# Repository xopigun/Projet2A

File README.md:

# Banc de test CAN — G69-BANC-001

Outil interne du **groupe 69** (ENSEA 2A, projet « Conception d'une Électronique Modulaire
(Bus CAN) ») servant à valider le standard CAN commun et les ICD produits avec les groupes
partenaires.

Le banc est **générique** : aucun code n'est spécifique à un groupe partenaire, les besoins
particuliers passent par de la configuration. Les quatre projets partenaires (Cobot RMD-X,
Ecomarathon, Formula Student, MIR1000) sont traités au même niveau.

Auteurs (ordre alphabétique) : Samuel GOMRI, Dylan KIATI, Hugo MATHOUX.

---

## ⚠ À faire avant la première mise sous tension

Ces deux points sont des **modifications matérielles** sur chaque Nucleo-G431KB. Les ignorer
donne des symptômes qui ressemblent à une panne et non à une erreur de montage.

1. **Retirer le cavalier HW1**, livré fermé entre `CN4` broche 5 (`D2` = PA12) et `CN4`
   broche 4 (`GND`) — UM2397 §5.1 et §6.1. PA12 est `FDCAN1_TX` : laissé à la masse, il
   place le bus en **état dominant permanent** et bloque toute communication.

2. **Souder les ponts SB9 et SB10** pour connecter le quartz 24 MHz. En sortie d'usine la
   carte démarre sur le **HSI** (UM2397 §6.5, Table 9), dont la précision de ±1 % dépasse
   plus du double la tolérance admissible de 0,485 % à 500 kbit/s. Tant que ce n'est pas
   fait, compiler avec `-DBENCH_CLOCK_SOURCE=HSI` : le firmware émet un avertissement à la
   compilation, affiche `HSI - NON VALIDE` sur l'écran et signale le défaut dans son
   heartbeat, et `canbench` refuse alors de prononcer un verdict de réussite.

**Procédure de mise en route pas à pas : [docs/bringup.md](docs/bringup.md).** Elle amène
trois cartes neuves à un bus qui communique, en validant l'horloge, le temps de bit et
l'encodage **avant** tout câblage grâce au bouclage interne du FDCAN.

Brochage, terminaisons et injection de fautes : [docs/pinout.md](docs/pinout.md).

---

## Démarrage rapide

### Prérequis

| Outil | Version | Rôle |
|---|---|---|
| git | ≥ 2.30 | sous-modules |
| CMake | ≥ 3.24 | presets version 6 |
| Ninja | ≥ 1.10 | générateur |
| `arm-none-eabi-gcc` | ≥ 12 | firmwares |
| `gcc` ou `clang` | — | tests unitaires natifs |
| Python | ≥ 3.10 | outils PC et génération depuis l'ICD |
| STM32CubeProgrammer **ou** OpenOCD | — | programmation (facultatif) |

### Cloner

```bash
git clone --recursive <url> banc-can
cd banc-can
```

Si le dépôt a été cloné sans `--recursive` :

```bash
git submodule update --init --recursive
```

### Compiler et exécuter les tests unitaires (aucun matériel)

```bash
cmake --preset host
cmake --build --preset host
ctest --preset host
```

### Compiler un firmware

Un preset par nœud : `n1`, `n2`, `n3` (Nucleo-G431KB) et `n4` (Blue Pill STM32F103).

```bash
cmake --preset n1
cmake --build --preset n1
```

### Programmer un nœud

```bash
cmake --build --preset n1 --target flash_n1
```

`STM32_Programmer_CLI` et `openocd` sont cherchés dans le `PATH` puis dans les emplacements
d'installation usuels ; le premier trouvé est utilisé. Pour forcer :
`cmake --preset n1 -DBENCH_FLASH_TOOL=openocd`.

### Installer les outils PC

```bash
python -m pip install -e "pc[dev]"
```

### Premier test, sans matériel

Toutes les sous-commandes fonctionnent sur le bus `virtual` de python-can, avec un
simulateur qui reproduit N1 à N4 (ARM/GO et heartbeat compris) :

```bash
canbench --interface virtual --simulate arbitration --cycles 100
canbench --interface virtual --simulate encoding
canbench --interface virtual --simulate faults
canbench --interface virtual --simulate busload --measure 2
```

`--simulate` démarre un simulateur reproduisant N1 à N4. **Aucun verdict de réussite n'est
prononcé sur le bus virtuel** : le simulateur reproduit le comportement attendu, il ne le
démontre pas. Les rapports produits portent la mention correspondante.

### Interface graphique

Pour une démonstration, ou simplement pour piloter le banc sans ligne de commande, il
existe un **logiciel Windows**, `BancCAN.exe`. Il s'ouvre dans sa propre fenêtre, se
connecte depuis le bouton « Connexion » (simulation ou CANable), et s'arrête quand on
ferme la fenêtre. Le bouton « Aide » explique chaque indicateur, chaque test et chaque
faute. L'exécutable n'est pas versionné ; il se reconstruit en une minute :

```bash
python -m pip install pyinstaller
```

```bash
python pc/build_exe.py
```

Le fichier produit est `dist/BancCAN.exe`. Pour que le logiciel pilote un CANable réel,
installer le pilote python-can correspondant **avant** de le construire
(`python -m pip install -e "pc[slcan]"` ou `"pc[gs-usb]"`) : il est alors embarqué.
Le firmware candleLight (`gs_usb`) demande en outre la bibliothèque système **libusb**,
absente par défaut sous Windows : installer `libusb-package` avant la construction, qui
embarque alors `libusb-1.0.dll`. Tant qu'elle manque, la fenêtre « Connexion »
l'indique au lieu de proposer une connexion vouée à l'échec. Le firmware `slcan` n'en a
pas besoin.

Sans construire l'exécutable, **double-cliquer sur `lancer_banc.bat`** donne la même
interface dans le navigateur. Le navigateur s'ouvre sur
<http://127.0.0.1:8765> et affiche le bus en direct, l'état des nœuds tiré de leurs
heartbeats, les trames décodées par l'ICD, les tests T3, T4 et T6 avec leur rapport
téléchargeable, et l'injection de fautes par `BENCH_CFG`.

Sans argument, l'interface tourne en **simulation** : un bandeau le rappelle en permanence
et aucun verdict n'y vaut preuve. Sur le banc réel :

```bash
lancer_banc.bat gs_usb
```

L'équivalent en ligne de commande est `canbench --interface virtual gui`. L'interface
n'ajoute aucune dépendance et n'a aucune logique de test propre : elle appelle les mêmes
fonctions que `canbench`.

### Premier test sur le banc réel

Le CANable 2.0 est supporté en firmware candleLight (`gs_usb`) et en `slcan` :

```bash
canbench --interface gs_usb  monitor
canbench --interface slcan --channel COM7 arbitration --cycles 1000
```

---

## Organisation du dépôt

| Répertoire | Contenu |
|---|---|
| `icd/` | `bench_icd.yaml` — **source unique** des identifiants, signaux et encodages |
| `tools/codegen/` | génération depuis l'ICD : C, Python, DBC, LaTeX |
| `firmware/common/` | code indépendant du microcontrôleur — aucun en-tête HAL |
| `firmware/ports/` | couches matérielles : `g431_fdcan`, `f103_bxcan` |
| `firmware/boards/` | `board.h` — **tout** le brochage, et nulle part ailleurs |
| `firmware/vendor/` | sous-modules ST épinglés (HAL, CMSIS) |
| `firmware/tests_host/` | tests unitaires natifs du code commun |
| `pc/canbench/` | outil en ligne de commande `canbench` |
| `scripts/` | `bit_timing.py`, `bus_load.py` |
| `docs/` | plan, architecture, brochage, bit timing, protocole de validation, extraits LaTeX |

Le code généré depuis l'ICD (`firmware/common/icd_gen/`, `pc/canbench/icd_gen.py`) **ne
doit pas être édité à la main** : un test de CI vérifie qu'il est à jour.

## Sous-modules

Versions épinglées ; licences relevées dans les dépôts aux versions indiquées.

| Sous-module | Tag | Licence |
|---|---|---|
| `cmsis_core` | `v5.9.0_20250520` | Apache-2.0 |
| `cmsis_device_g4` | `v1.2.6` | Apache-2.0 |
| `cmsis_device_f1` | `v4.3.5` | Apache-2.0 |
| `stm32g4xx_hal_driver` | `v1.2.7` | BSD-3-Clause |
| `stm32f1xx_hal_driver` | `v1.1.10` | BSD-3-Clause |

Le projet lui-même est sous licence MIT — voir [LICENSE](LICENSE).

## Paramètres retenus

| Paramètre | Valeur |
|---|---|
| Débit | 500 kbit/s, CAN 2.0A *classic* (identifiants 11 bits) |
| Point d'échantillonnage | 87,50 % exactement, identique sur G431 et F103 |
| Tolérance d'oscillateur | 0,485 % — voir [docs/bit_timing.md](docs/bit_timing.md) |
| G431 | horloge FDCAN 80 MHz, BRP 10, 16 tq (1+13+2), SJW 2 |
| F103 | APB1 36 MHz, BRP 9, 8 tq (1+6+1), SJW 1 |

## Documentation

- [docs/PLAN.md](docs/PLAN.md) — plan de travail, écarts relevés, points à vérifier
- [docs/architecture.md](docs/architecture.md) — couches, flux ISR, machine d'états ARM/GO
- [docs/pinout.md](docs/pinout.md) — brochage, vérifié depuis les `board.h`
- [docs/bit_timing.md](docs/bit_timing.md) — calcul et justification du bit timing
- [docs/config_logicielle.md](docs/config_logicielle.md) — paramètres FDCAN/bxCAN
- [docs/protocole_validation.md](docs/protocole_validation.md) — les sept tests T1 à T7
- [docs/bringup.md](docs/bringup.md) — procédure de mise en route pas à pas
- [docs/references/README.md](docs/references/README.md) — où trouver les documents de référence

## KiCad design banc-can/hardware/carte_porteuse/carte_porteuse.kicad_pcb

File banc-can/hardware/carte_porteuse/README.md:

# Carte porteuse d'un nœud du banc CAN (v0.2)

Une Nucleo-G431KB s'enfiche dessus. La carte porte le transceiver TJA1051T/3 et ses
découplages, deux borniers pour chaîner le bus (entrée à gauche, sortie à droite), la
terminaison 120 Ω sur cavalier, l'écran OLED, le MPU-6050 (N2) et deux LED d'état.
Plus aucun fil Dupont. À fabriquer en 4 exemplaires.

## Disposition (vue de dessus, arrière en haut)

| Zone | Contenu |
|---|---|
| Bande arrière | bornier d'entrée (fils à gauche), bornier de sortie (fils à droite), fixation M3 H1 |
| Colonne centrale | barrettes de la Nucleo, posée dans la profondeur, **USB vers l'arrière** (câble vers le hub) ; sous elle, le TJA1051, ses 100 nF, les résistances et la fixation H2 ; barrette coudée de l'OLED au bord avant |
| Gauche | barrette coudée du MPU-6050 : le module tient debout au-delà du bord |
| Droite | cavalier TERM, barrette capteurs (non montée), LED **B** (bus-off, jaune) et **E** (erreur, rouge) |

Contour en escalier : 2 050 mm² au lieu de 3 250 mm² pour la v0.1 rectangulaire (−37 %).

## Montage

1. Souder les CMS (U1, C1, C2, R1, R2, R3, R7, R9, R10, D1, D2), puis les barrettes et les borniers.
2. **Avant R9 et R10 : vérifier l'ordre des broches de l'OLED reçu.** GND puis VCC : R9 et R10.
   VCC puis GND : R11 et R12 à la place. Jamais les quatre.
3. Visser la carte sur la plaque du banc (H1, H2, vis M3), **puis** enficher la Nucleo :
   broche 1 de CN3 et CN4 côté USB, flèche « ^ USB ».
4. L'OLED s'enfiche à l'horizontale dans sa barrette coudée et tient debout, à l'envers :
   le firmware retourne l'affichage. Le MPU-6050 de même, sur N2.
5. Cavalier TERM sur le nœud en bout de bus seulement (N4 : câble vers l'interrupteur SW1).

Non montés : R8 (S sur PB6), R11/R12 (OLED en VCC/GND), R4/R5 (tirages I2C, les modules ont
les leurs), J8 (capteurs Hall et 1-Wire, reportés ; tirage 1-Wire sur le module DS18B20).

## Vérifications

**Électrique** : ERC 0 ; DRC 0 erreur, 0 liaison manquante, 0 erreur d'empreinte ; restent
79 avertissements de sérigraphie (contours des barrettes coudées et des borniers qui touchent
volontairement le bord, repères qui se touchent).

**Encombrements** (`verification/encombrement.py`, sur l'export 3D KiCad) : aucun conflit entre
les modules enfichés (Nucleo et sa fiche USB, OLED debout, MPU-6050 debout, fils des borniers,
cavalier, câble capteurs, têtes de vis M3) et les composants. Sous la Nucleo (fond à 10,5 mm),
le plus haut est le corps de la barrette OLED (4,1 mm). Le MPU-6050 commence 2,7 mm sous les
fils du bornier d'entrée. Vue : `openscad verification/assemblage.scad` après
`kicad-cli pcb export stl --subst-models --user-origin 100x100mm -o verification/carte.stl carte_porteuse.kicad_pcb`.

**Solidité** : largeur minimale 19,6 mm ; les parties latérales sont rattachées au corps sur
toute leur longueur (22 et 45 mm) ; deux angles rentrants seulement, loin des borniers ; les
deux vis M3 sont entre les barrettes de la Nucleo, là où s'exerce l'effort d'enfichage. La
plaque du banc devra soutenir les deux coins arrière, sous les borniers, où l'on serre les vis.

**Cours PCB (option Maker)** :

| Règle du cours | Sur la carte |
|---|---|
| Contraintes mécaniques et fixations d'abord | 2 trous M3 de 3,2 mm (admis par la factory), placés en premier |
| Connecteurs au bord, câbles vers l'extérieur | borniers sur les bords gauche et droit, USB vers l'arrière, modules debout au-delà des bords |
| Microcontrôleur au centre, composants près de leurs broches | Nucleo au centre ; LED près de PA0/PA1 (CN3), MPU près de l'I2C (CN4) |
| Découplage au plus près | 100 nF à 2,5 mm de VCC et 2,9 mm de VIO |
| Plan de masse | deux faces, masse aussi routée sous la Nucleo ; vias de masse superflus retirés (`../elaguer_vias.py`), puis vias de couture posés à la main : 34 vias au total. Relancer `route_freerouting.py` remettrait les vias automatiques |
| Classes de nets, pistes larges pour l'alimentation | classe Puissance : +5V et +3V3 en 0,6 mm, signaux en 0,4 mm |
| Teardrops | 99 |
| Champ MPN dans les symboles | 26 composants renseignés |
| ERC et DRC propres | voir plus haut |
| Règles factory | piste 0,4 mm, isolation 0,3 mm, vias 0,8/0,4 mm, 0,5 mm au contour, 0805 HandSolder |
| Le plus petit possible, pas de gaspillage | contour découpé ; seules les barrettes de la Nucleo ont des broches inutilisées (elles la tiennent) |

À confirmer avec la factory : la découpe d'un contour non rectangulaire (angles rentrants).

## Régénérer

`generate_schematic.py` → `generate_pcb.py` → `route_freerouting.py <freerouting.jar>` →
teardrops dans l'éditeur de PCB (Éditer > Éditer Teardrops) → `generate_fabrication.py`
(depuis PowerShell) → `generate_commande.py`.

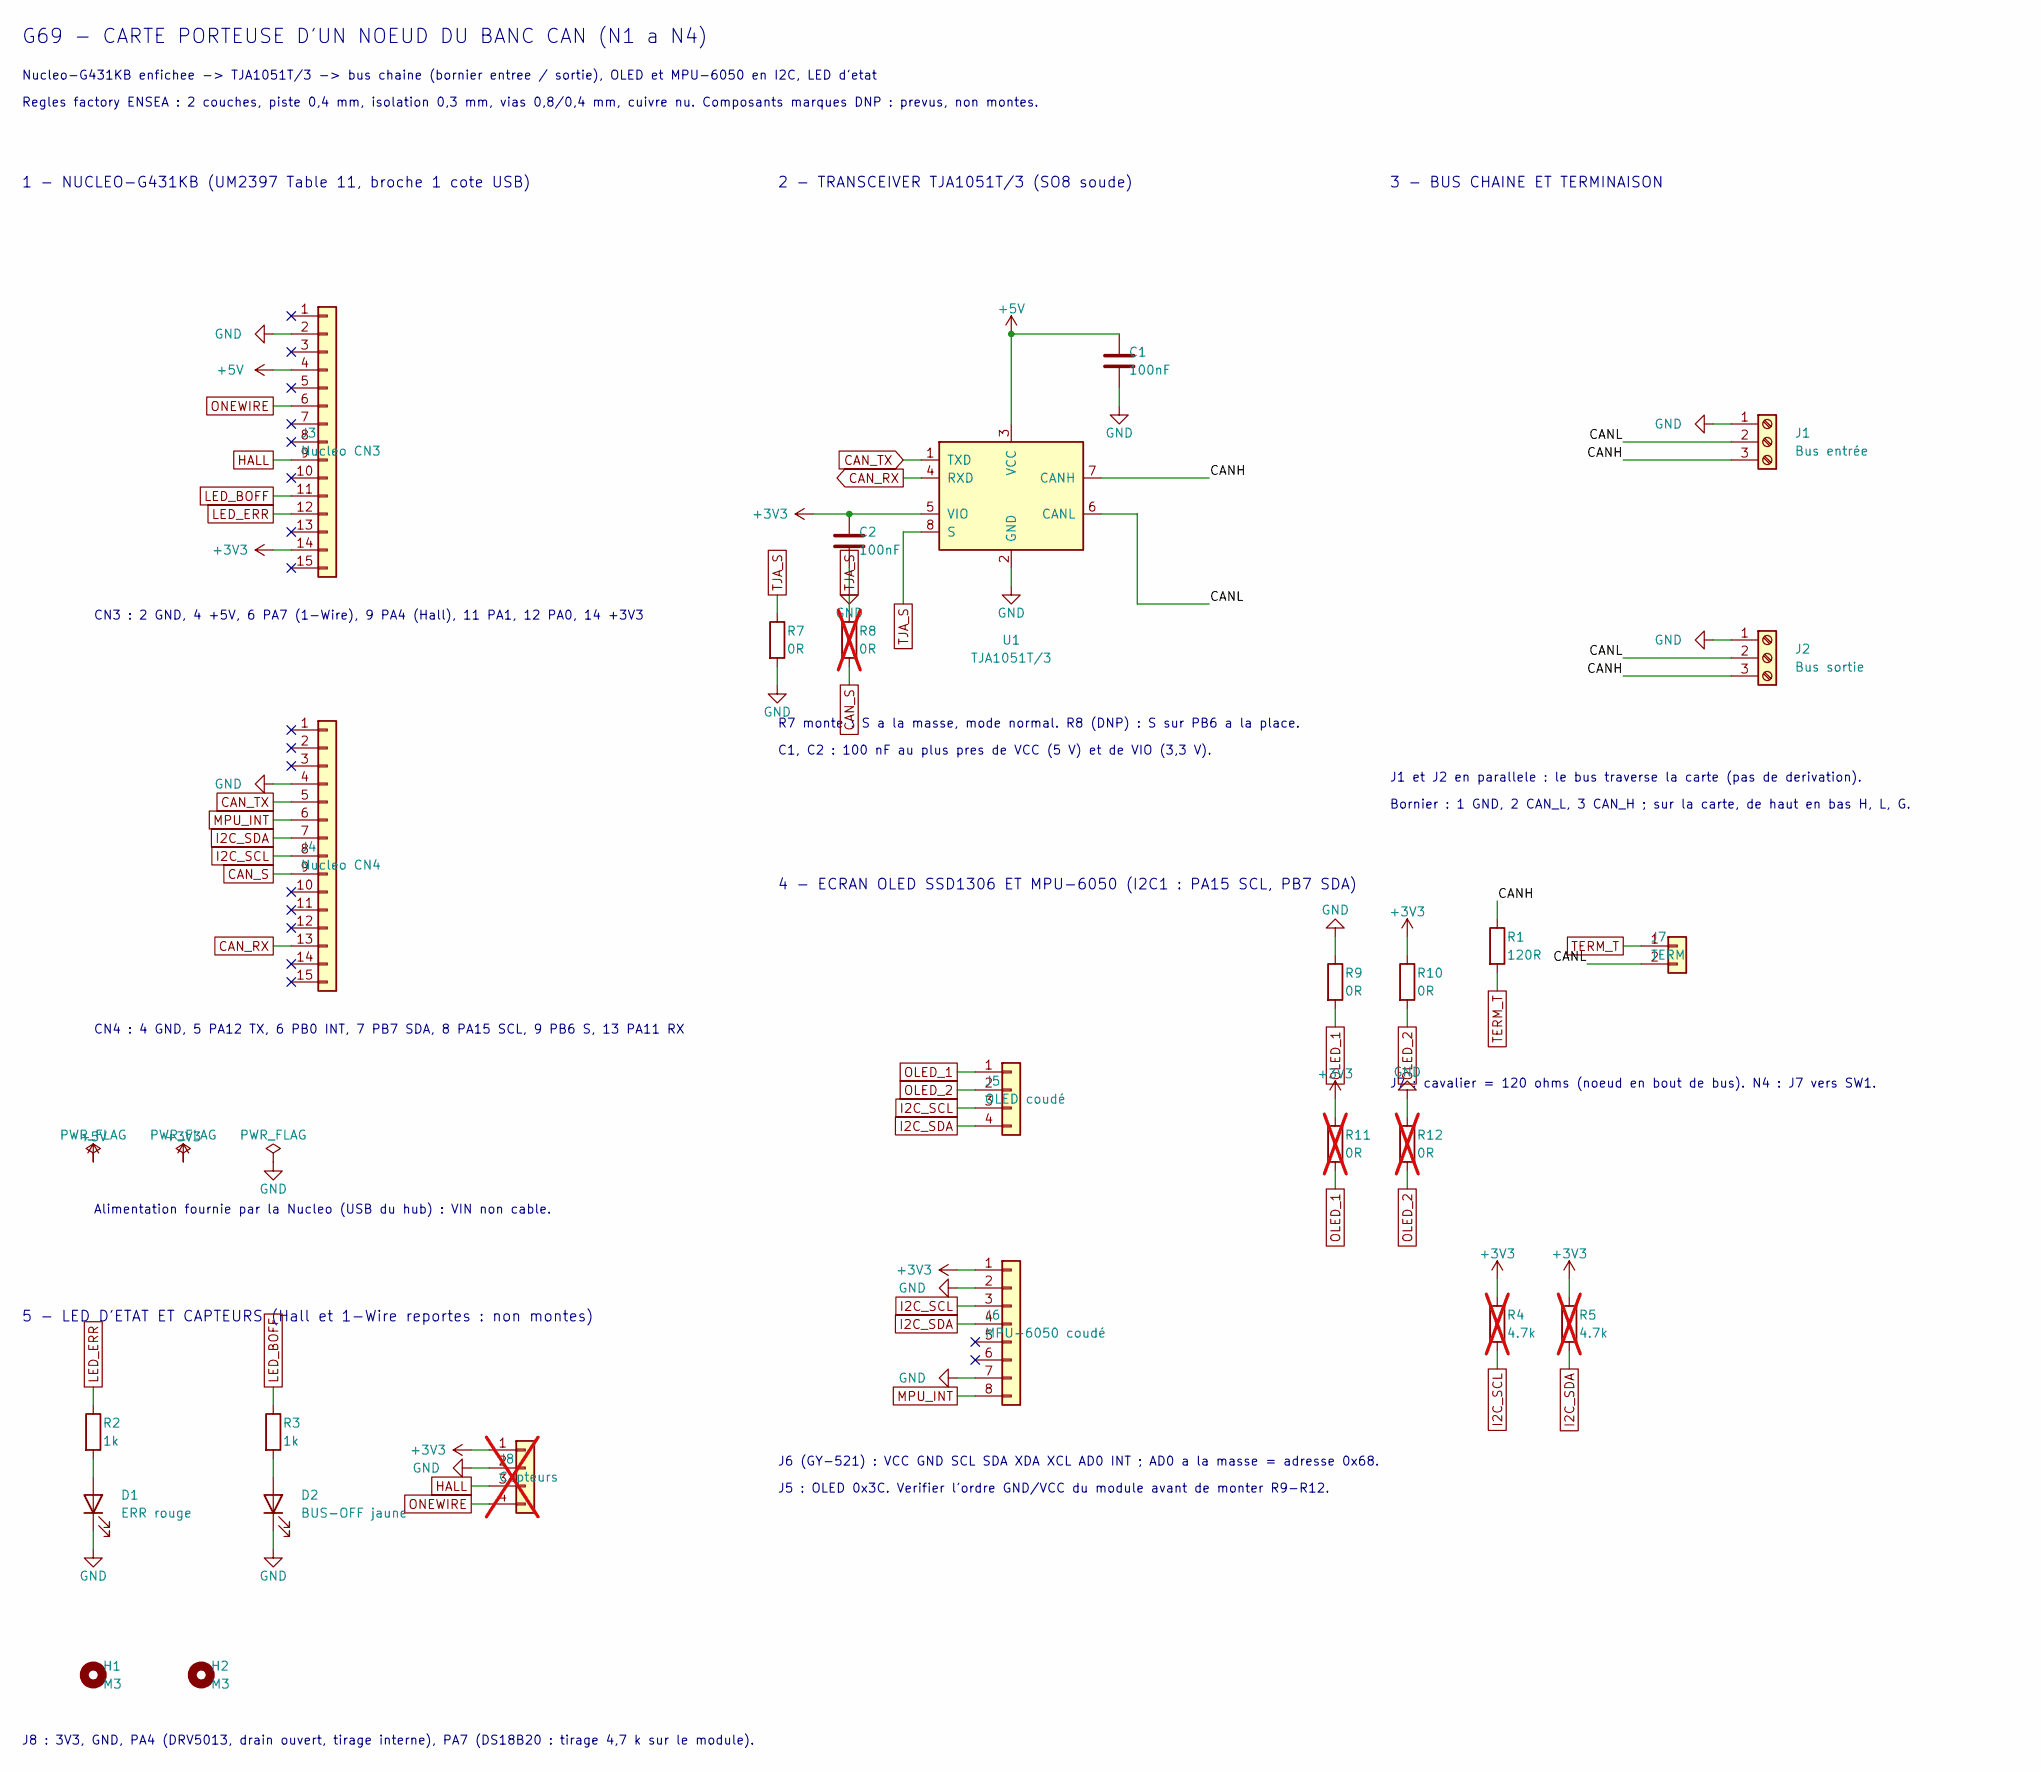
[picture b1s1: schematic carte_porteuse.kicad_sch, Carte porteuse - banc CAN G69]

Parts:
C1, C2: 100nF; C_0805_2012Metric_Pad1.18x1.45mm_HandSolder; MPN CL21B104KBCNNNC
D1: ERR rouge; LED_0805_2012Metric_Pad1.15x1.40mm_HandSolder; MPN 150080RS75000
D2: BUS-OFF jaune; LED_0805_2012Metric_Pad1.15x1.40mm_HandSolder; MPN 150080YS75000
H1, H2: M3; MountingHole_3.2mm_M3; MPN trou de fixation 3,2 mm, vis M3
J1: Bus entrée; TerminalBlock_Phoenix_MKDS-1,5-3-5.08_1x03_P5.08mm_Horizont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; MPN 1729131 (MKDS 1,5/ 3-5,08)
J2: Bus sortie; TerminalBlock_Phoenix_MKDS-1,5-3-5.08_1x03_P5.08mm_Horizont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; MPN 1729131 (MKDS 1,5/ 3-5,08)
J3: Nucleo CN3; PinSocket_1x15_P2.54mm_Vertical; MPN barrette femelle 1 x 15, pas 2,54 mm
J4: Nucleo CN4; PinSocket_1x15_P2.54mm_Vertical; MPN barrette femelle 1 x 15, pas 2,54 mm
J5: OLED coudé; PinSocket_1x04_P2.54mm_Horizontal; MPN barrette femelle coudée 1 x 4, pas 2,54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
J6: MPU-6050 coudé; PinSocket_1x08_P2.54mm_Horizontal; MPN barrette femelle coudée 1 x 8, pas 2,54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
J7: TERM; PinHeader_1x02_P2.54mm_Vertical; MPN 61300211121
J8: Capteurs; PinHeader_1x04_P2.54mm_Vertical; MPN barrette mâle 1 x 4, pas 2,54 mm; not fitted
R1: 120R; R_0805_2012Metric_Pad1.20x1.40mm_HandSolder; MPN RC0805FR-07120RL
R2, R3: 1k; R_0805_2012Metric_Pad1.20x1.40mm_HandSolder; MPN RC0805FR-071KL
R4, R5: 4.7k; R_0805_2012Metric_Pad1.20x1.40mm_HandSolder; MPN RC0805FR-074K7L; not fitted
R7, R9, R10: 0R; R_0805_2012Metric_Pad1.20x1.40mm_HandSolder; MPN RC0805JR-070RL
R8, R11, R12: 0R; R_0805_2012Metric_Pad1.20x1.40mm_HandSolder; MPN RC0805JR-070RL; not fitted
U1: TJA1051T/3; SOIC-8_3.9x4.9mm_P1.27mm; MPN TJA1051T/3,118

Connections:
+3V3: C2.1, J3.14, J6.1, J8.1, R4.1, R5.1, R10.1, R11.1, U1.5 (VIO)
+5V: C1.1, J3.4, U1.3 (VCC)
/CANH: J1.3, J2.3, R1.1, U1.7 (CANH)
/CANL: J1.2, J2.2, J7.2, U1.6 (CANL)
CAN_RX: J4.13, U1.4 (RXD)
CAN_S: J4.9, R8.2
CAN_TX: J4.5, U1.1 (TXD)
GND: C1.2, C2.2, D1.1 (K), D2.1 (K), J1.1, J2.1, J3.2, J4.4, J6.2, J6.7, J8.2, R7.2, R9.1, R12.1, U1.2 (GND)
HALL: J3.9, J8.3
I2C_SCL: J4.8, J5.3, J6.3, R4.2
I2C_SDA: J4.7, J5.4, J6.4, R5.2
LED_BOFF: J3.11, R3.1
LED_ERR: J3.12, R2.1
MPU_INT: J4.6, J6.8
unnamed: D1.2 (A), R2.2
unnamed: D2.2 (A), R3.2
OLED_1: J5.1, R9.2, R11.2
OLED_2: J5.2, R10.2, R12.2
ONEWIRE: J3.6, J8.4
TERM_T: J7.1, R1.2
TJA_S: R7.1, R8.1, U1.8 (S)

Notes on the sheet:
G69 - CARTE PORTEUSE D'UN NOEUD DU BANC CAN (N1 a N4)
Nucleo-G431KB enfichee -> TJA1051T/3 -> bus chaine (bornier entree / sortie), OLED et MPU-6050 en I2C, LED d'etat
Regles factory ENSEA : 2 couches, piste 0,4 mm, isolation 0,3 mm, vias 0,8/0,4 mm, cuivre nu. Composants marques DNP : prevus, non montes.
1 - NUCLEO-G431KB (UM2397 Table 11, broche 1 cote USB)
CN3 : 2 GND, 4 +5V, 6 PA7 (1-Wire), 9 PA4 (Hall), 11 PA1, 12 PA0, 14 +3V3
CN4 : 4 GND, 5 PA12 TX, 6 PB0 INT, 7 PB7 SDA, 8 PA15 SCL, 9 PB6 S, 13 PA11 RX
Alimentation fournie par la Nucleo (USB du hub) : VIN non cable.
2 - TRANSCEIVER TJA1051T/3 (SO8 soude)
R7 monte : S a la masse, mode normal. R8 (DNP) : S sur PB6 a la place.
C1, C2 : 100 nF au plus pres de VCC (5 V) et de VIO (3,3 V).
3 - BUS CHAINE ET TERMINAISON
J1 et J2 en parallele : le bus traverse la carte (pas de derivation).
Bornier : 1 GND, 2 CAN_L, 3 CAN_H ; sur la carte, de haut en bas H, L, G.
J7 : cavalier = 120 ohms (noeud en bout de bus). N4 : J7 vers SW1.
4 - ECRAN OLED SSD1306 ET MPU-6050 (I2C1 : PA15 SCL, PB7 SDA)
J6 (GY-521) : VCC GND SCL SDA XDA XCL AD0 INT ; AD0 a la masse = adresse 0x68.
J5 : OLED 0x3C. Verifier l'ordre GND/VCC du module avant de monter R9-R12.
5 - LED D'ETAT ET CAPTEURS (Hall et 1-Wire reportes : non montes)
J8 : 3V3, GND, PA4 (DRV5013, drain ouvert, tirage interne), PA7 (DS18B20 : tirage 4,7 k sur le module).

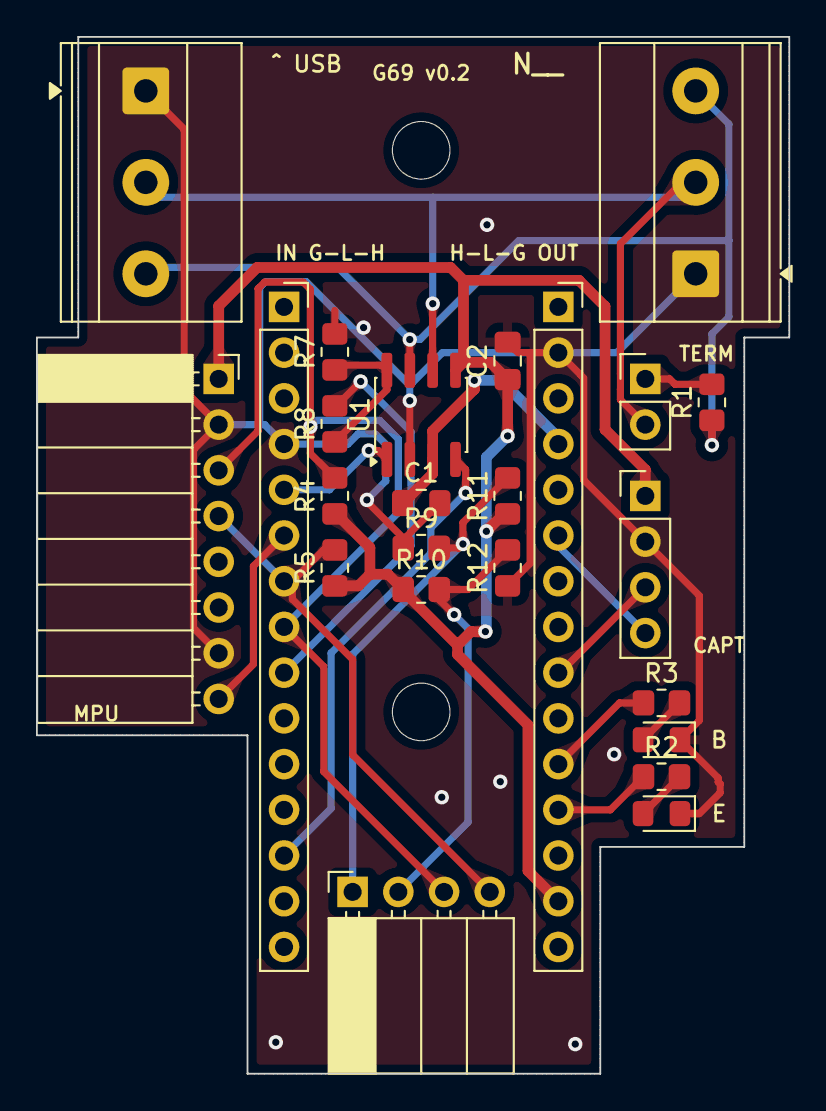
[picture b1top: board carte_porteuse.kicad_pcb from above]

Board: 2 copper layers, 41.8 x 57.6 mm, 26 parts (0 on the bottom side), 21 nets.

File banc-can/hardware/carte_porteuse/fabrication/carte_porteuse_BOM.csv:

Qté;Repères;Désignation;Valeur;Boîtier;Remarque
2;C1, C2;Condensateur céramique X7R 50 V;100nF;0805;découplage VCC et VIO du transceiver
1;D1;LED rouge;ERR rouge;0805;error-passive
1;D2;LED jaune;BUS-OFF jaune;0805;bus-off
1;J1;Bornier à vis 3 points, pas 5,08 mm (type Phoenix MKDS 1,5/3-5,08);Bus entrée;traversant;bus CAN : H, L, G
1;J2;Bornier à vis 3 points, pas 5,08 mm (type Phoenix MKDS 1,5/3-5,08);Bus sortie;traversant;bus CAN : H, L, G
1;J3;Barrette femelle 1 x 15, pas 2,54 mm;Nucleo CN3;traversant;reçoit la Nucleo-G431KB
1;J4;Barrette femelle 1 x 15, pas 2,54 mm;Nucleo CN4;traversant;reçoit la Nucleo-G431KB
1;J5;Barrette femelle coudée 1 x 4, pas 2,54 mm;OLED coudé;traversant;"écran OLED SSD1306 0,96"" debout au bord avant"
1;J6;Barrette femelle coudée 1 x 8, pas 2,54 mm;MPU-6050 coudé;traversant;module GY-521 debout au bord gauche, N2 seulement
1;J7;Barrette mâle 1 x 2, pas 2,54 mm + cavalier;TERM;traversant;"terminaison 120 ohms ; sur N4, câblée vers SW1"
1;R1;Résistance 1 %, 1/8 W;120R;0805;terminaison CAN, active avec un cavalier sur TERM
2;R2, R3;Résistance 1 %, 1/8 W;1k;0805;LED
3;R7, R9, R10;Résistance 0 ohm (ou strap);0R;0805;"R7 : broche S à la masse ; R9, R10 : ordre GND/VCC de l'OLED (à vérifier)"
1;U1;Transceiver CAN TJA1051T/3, SOIC-8;TJA1051T/3;SOIC-8;suffixe /3 : broche VIO (3,3 V)

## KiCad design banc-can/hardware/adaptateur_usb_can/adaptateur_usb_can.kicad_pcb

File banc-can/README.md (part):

# Banc de test CAN — G69-BANC-001

Outil interne du **groupe 69** (ENSEA 2A, projet « Conception d'une Électronique Modulaire
(Bus CAN) ») servant à valider le standard CAN commun et les ICD produits avec les groupes
partenaires.

Le banc est **générique** : aucun code n'est spécifique à un groupe partenaire, les besoins
particuliers passent par de la configuration. Les quatre projets partenaires (Cobot RMD-X,
Ecomarathon, Formula Student, MIR1000) sont traités au même niveau.

Auteurs (ordre alphabétique) : Samuel GOMRI, Dylan KIATI, Hugo MATHOUX.

**État du projet, choix abandonnés et prochaines étapes : [docs/ETAT_PROJET.md](docs/ETAT_PROJET.md).**

---

## ⚠ À faire avant la première mise sous tension

Ces deux points sont des **modifications matérielles** sur chaque Nucleo-G431KB. Les ignorer
donne des symptômes qui ressemblent à une panne et non à une erreur de montage.

1. **Retirer le cavalier HW1**, livré fermé entre `CN4` broche 5 (`D2` = PA12) et `CN4`
   broche 4 (`GND`) — UM2397 §5.1 et §6.1. PA12 est `FDCAN1_TX` : laissé à la masse, il
   place le bus en **état dominant permanent** et bloque toute communication.

2. **Souder les ponts SB9 et SB10** pour connecter le quartz 24 MHz. En sortie d'usine la
   carte démarre sur le **HSI** (UM2397 §6.5, Table 9), dont la précision de ±1 % dépasse
   plus du double la tolérance admissible de 0,485 % à 500 kbit/s. Tant que ce n'est pas
   fait, compiler avec `-DBENCH_CLOCK_SOURCE=HSI` : le firmware émet un avertissement à la
   compilation, affiche `HSI - NON VALIDE` sur l'écran et signale le défaut dans son
   heartbeat, et `canbench` refuse alors de prononcer un verdict de réussite.

**Procédure de mise en route pas à pas : [docs/bringup.md](docs/bringup.md).** Elle amène
trois cartes neuves à un bus qui communique, en validant l'horloge, le temps de bit et
l'encodage **avant** tout câblage grâce au bouclage interne du FDCAN.

Brochage, terminaisons et injection de fautes : [docs/pinout.md](docs/pinout.md).

---

## Démarrage rapide

### Prérequis

| Outil | Version | Rôle |
|---|---|---|
| git | ≥ 2.30 | sous-modules |
| CMake | ≥ 3.24 | presets version 6 |
| Ninja | ≥ 1.10 | générateur |
| `arm-none-eabi-gcc` | ≥ 12 | firmwares |
| `gcc` ou `clang` | — | tests unitaires natifs |
| Python | ≥ 3.10 | outils PC et génération depuis l'ICD |
| STM32CubeProgrammer **ou** OpenOCD | — | programmation (facultatif) |

### Cloner

```bash
git clone --recursive <url> banc-can
cd banc-can
```

Si le dépôt a été cloné sans `--recursive` :

```bash
git submodule update --init --recursive
```

### Compiler et exécuter les tests unitaires (aucun matériel)

```bash
cmake --preset host
cmake --build --preset host
ctest --preset host
```

### Compiler un firmware

Un preset par nœud : `n1` à `n4`, quatre Nucleo-G431KB.

```bash
cmake --preset n1
cmake --build --preset n1
```

### Programmer un nœud

```bash
cmake --build --preset n1 --target flash_n1
```

`STM32_Programmer_CLI` et `openocd` sont cherchés dans le `PATH` puis dans les emplacements
d'installation usuels ; le premier trouvé est utilisé. Pour forcer :
`cmake --preset n1 -DBENCH_FLASH_TOOL=openocd`.

**Plusieurs cartes branchées à la fois** : sans autre précision, l'outil programme la
première sonde trouvée, pas forcément le nœud visé. Lister les sondes, puis fixer une fois
pour toutes le numéro de série de chaque nœud :

```bash
STM32_Programmer_CLI --list st-link
```

```bash
cmake --preset n1-scope-direct -DBENCH_STLINK_SN=005000463335510433383531
```

### Installer les outils PC

```bash
python -m pip install -e "pc[dev]"
```

### Premier test, sans matériel

Toutes les sous-commandes fonctionnent sur le bus `virtual` de python-can, avec un
simulateur qui reproduit N1 à N4 (ARM/GO et heartbeat compris) :

```bash
canbench --interface virtual --simulate arbitration --cycles 100
canbench --interface virtual --simulate encoding
canbench --interface virtual --simulate faults
canbench --interface virtual --simulate busload --measure 2
```

`--simulate` démarre un simulateur reproduisant N1 à N4. **Aucun verdict de réussite n'est
prononcé sur le bus virtuel** : le simulateur reproduit le comportement attendu, il ne le
démontre pas. Les rapports produits portent la mention correspondante.

### Interface graphique

Pour une démonstration, ou simplement pour piloter le banc sans ligne de commande, il
existe un **logiciel Windows**, `BancCAN.exe`. Il s'ouvre dans sa propre fenêtre, se
connecte depuis le bouton « Connexion » (simulation ou CANable), et s'arrête quand on
ferme la fenêtre. Le bouton « Aide » explique chaque indicateur, chaque test et chaque
faute. L'exécutable n'est pas versionné ; il se reconstruit en une minute :

```bash
python -m pip install pyinstaller
```

```bash
python pc/build_exe.py
```

Le fichier produit est `dist/BancCAN.exe`. Pour que le logiciel pilote un CANable réel,
installer le pilote python-can correspondant **avant** de le construire
(`python -m pip install -e "pc[slcan]"` ou `"pc[gs-usb]"`) : il est alors embarqué.
Le firmware candleLight (`gs_usb`) demande en outre la bibliothèque système **libusb**,
absente par défaut sous Windows : installer `libusb-package` avant la construction, qui
embarque alors `libusb-1.0.dll`. Tant qu'elle manque, la fenêtre « Connexion »
l'indique au lieu de proposer une connexion vouée à l'échec. Le firmware `slcan` n'en a
pas besoin.

Sans construire l'exécutable, **double-cliquer sur `lancer_banc.bat`** donne la même
interface dans le navigateur. Le navigateur s'ouvre sur
<http://127.0.0.1:8765> et affiche le bus en direct, l'état des nœuds tiré de leurs
heartbeats, les trames décodées par l'ICD, les tests T3, T4 et T6 avec leur rapport
téléchargeable, et l'injection de fautes par `BENCH_CFG`.

Sans argument, l'interface tourne en **simulation** : un bandeau le rappelle en permanence
et aucun verdict n'y vaut preuve. Sur le banc réel :

```bash
lancer_banc.bat gs_usb
```

L'équivalent en ligne de commande est `canbench --interface virtual gui`. L'interface
n'ajoute aucune dépendance et n'a aucune logique de test propre : elle appelle les mêmes
fonctions que `canbench`.

### Premier test sur le banc réel

Le CANable 2.0 est supporté en firmware candleLight (`gs_usb`) et en `slcan` :

```bash
canbench --interface gs_usb  monitor
canbench --interface slcan --channel COM7 arbitration --cycles 1000
```

### Adaptateur ZLG USBCAN-UC12 (sans désactiver l'intégrité de la mémoire)

Le pilote noyau fourni par ZLG (`usbcan.sys`, 2017) est refusé par l'**intégrité de la
mémoire** de Windows. Le banc ne s'en sert pas : `pc/canbench/zlg_usbcan/` parle à
l'adaptateur directement, à travers **WinUSB**, le pilote générique signé par Microsoft.
Le protocole a été reconstitué pour l'interopérabilité ; il est décrit dans
[`PROTOCOLE.md`](pc/canbench/zlg_usbcan/PROTOCOLE.md).

Mise en place, une seule fois :

1. Gestionnaire de périphériques, sur l'adaptateur : *Mettre à jour le pilote* >
   *Choisir parmi la liste* > **Périphérique WinUsb**.
2. Installer les dépendances :

```bash
python -m pip install -e "pc[zlg]"
```

Ensuite :

```bash
canbench --interface zlg monitor
```

```bash
lancer_banc.bat zlg
```

Dans l'interface graphique, le panneau **Qualité** affiche alors l'état du contrôleur de
l'adaptateur (REC/TEC, error-active/warning/passive), ses événements d'erreur, les trames
émises que personne n'acquitte, et, pour chaque identifiant, la période, la gigue et les
trames manquées, mesurées sur l'horodatage matériel à 0,1 ms. Le type d'erreur CAN
(bourrage, CRC…) n'est pas disponible sur cet adaptateur. L'outil bas niveau
`python -m canbench.zlg_usbcan probe` interroge l'adaptateur sans passer par le banc.

---

## Organisation du dépôt

| Répertoire | Contenu |
|---|---|
| `icd/` | `bench_icd.yaml` — **source unique** des identifiants, signaux et encodages |
| `tools/codegen/` | génération depuis l'ICD : C, Python, DBC, LaTeX |
| `firmware/common/` | code indépendant du microcontrôleur — aucun en-tête HAL |
| `firmware/ports/` | couche matérielle : `g431_fdcan` (FDCAN du STM32G431) |
| `firmware/boards/` | `board.h` — **tout** le brochage, et nulle part ailleurs |
| `firmware/vendor/` | sous-modules ST épinglés (HAL, CMSIS) |
| `firmware/tests_host/` | tests unitaires natifs du code commun |
| `pc/canbench/` | outil en ligne de commande `canbench` |
| `scripts/` | `bit_timing.py`, `bus_load.py` |
| `docs/` | état du projet, plan, brochage, bit timing, protocole de validation, extraits LaTeX |
| `hardware/` | adaptateur USB-CAN (KiCad, fabrication, boîtier 3D), schéma de câblage du bus |
| `simulation_3d/` | banc complet en 3D dans le navigateur, moteur CAN au bit près |

Le code généré depuis l'ICD (`firmware/common/icd_gen/`, `pc/canbench/icd_gen.py`) **ne
doit pas être édité à la main** : un test de CI vérifie qu'il est à jour.

## Sous-modules

Versions épinglées ; licences relevées dans les dépôts aux versions indiquées.

| Sous-module | Tag | Licence |
|---|---|---|
| `cmsis_core` | `v5.9.0_20250520` | Apache-2.0 |
| `cmsis_device_g4` | `v1.2.6` | Apache-2.0 |
| `cmsis_device_l4` | `v1.7.5` | Apache-2.0 |
| `stm32g4xx_hal_driver` | `v1.2.7` | BSD-3-Clause |
| `stm32l4xx_hal_driver` | `v1.13.6` | BSD-3-Clause |

Le projet lui-même est sous licence MIT — voir [LICENSE](LICENSE).

## Paramètres retenus

| Paramètre | Valeur |
|---|---|
| Débit | 500 kbit/s, CAN 2.0A *classic* (identifiants 11 bits) |
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
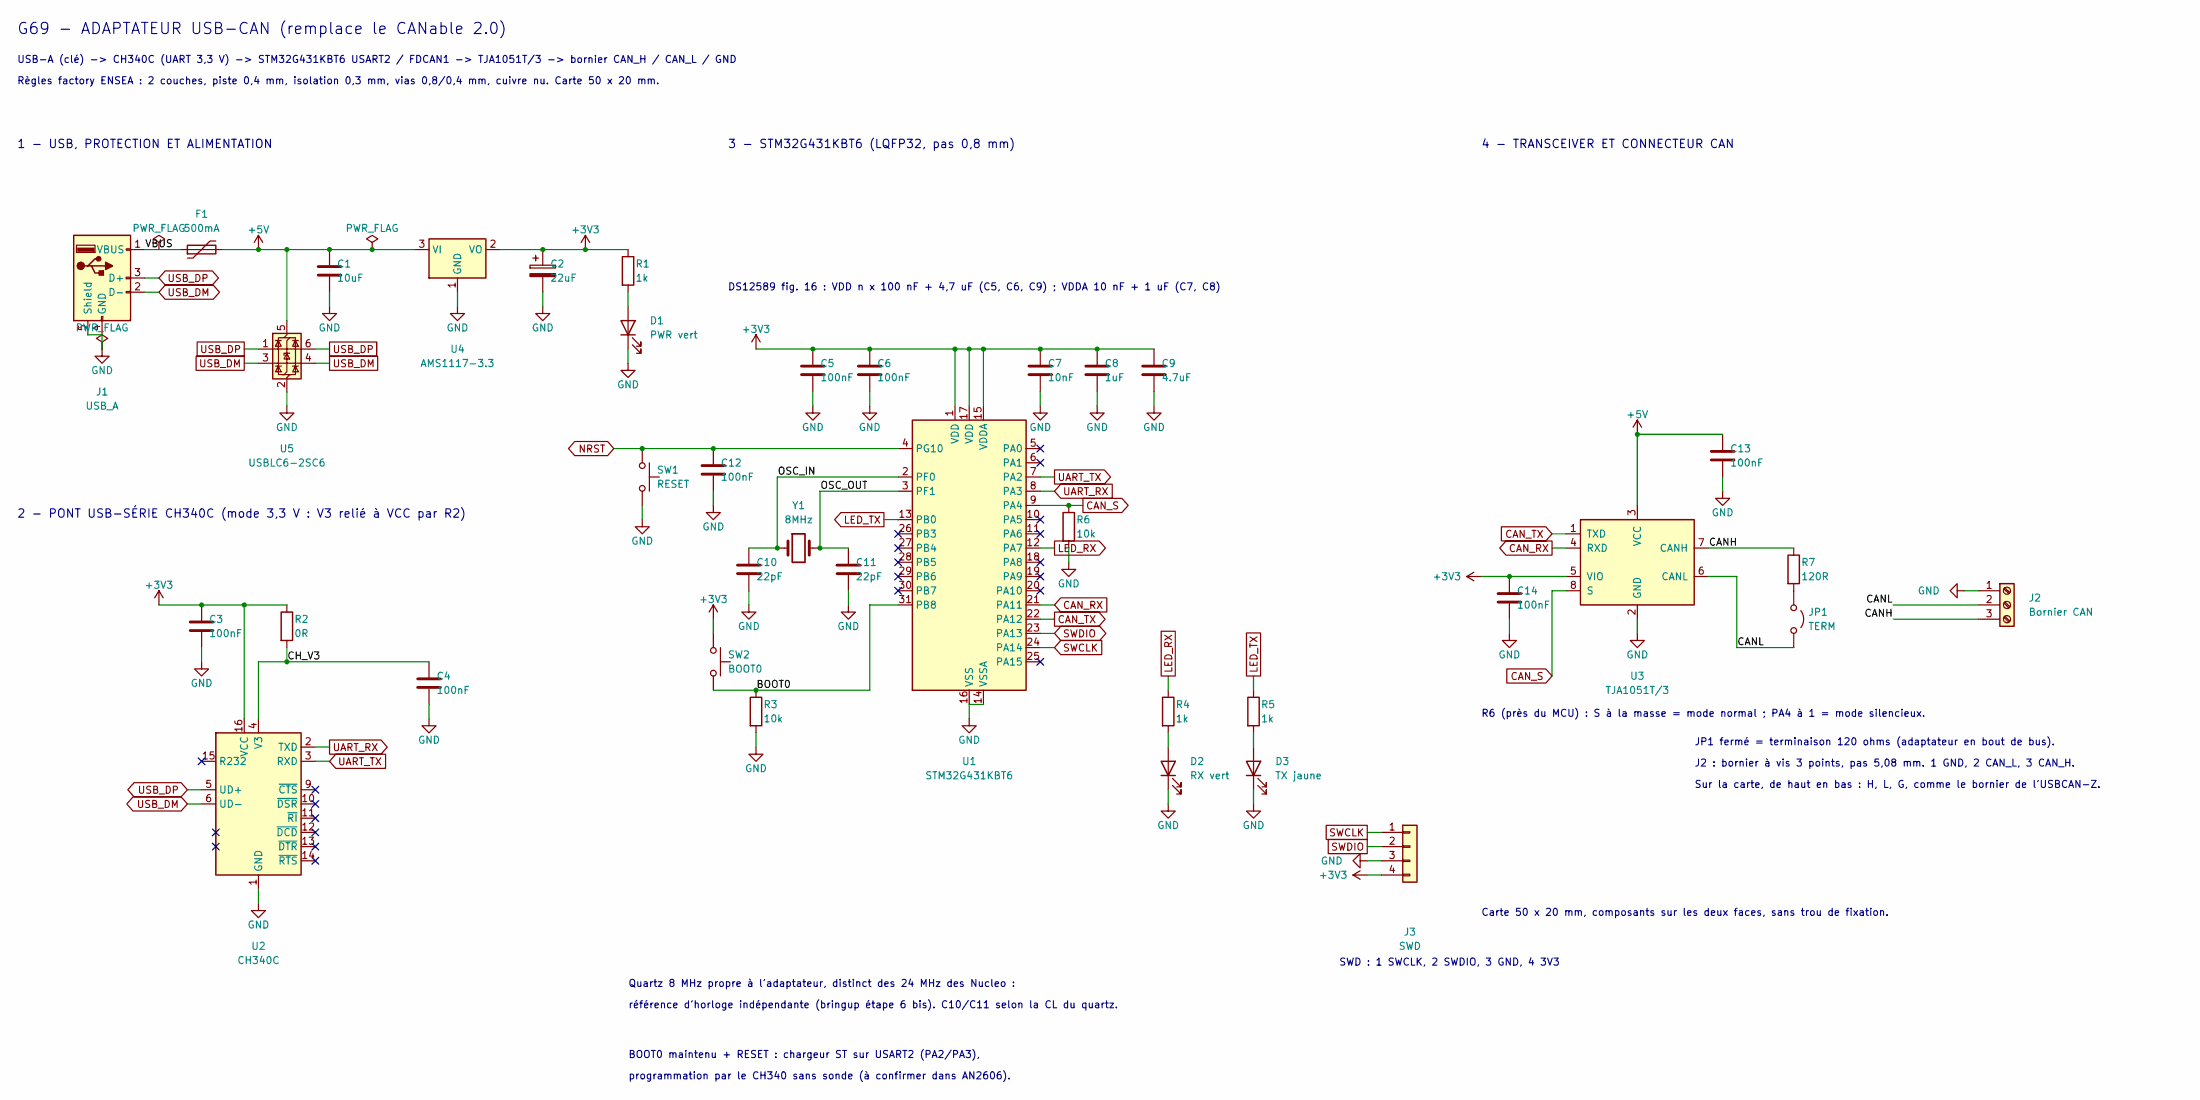
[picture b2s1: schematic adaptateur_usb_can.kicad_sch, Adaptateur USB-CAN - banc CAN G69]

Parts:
C1: 10uF; C_0805_2012Metric_Pad1.18x1.45mm_HandSolder; MPN CL21A106KOQNNNE
C2: 22uF; CP_EIA-3216-18_Kemet-A_HandSolder; MPN T491A226K010AT
C3, C4, C5, C6, C12, C13, C14: 100nF; C_0805_2012Metric_Pad1.18x1.45mm_HandSolder; MPN CL21B104KBCNNNC
C7: 10nF; C_0805_2012Metric_Pad1.18x1.45mm_HandSolder; MPN CL21B103KBANNNC
C8: 1uF; C_0805_2012Metric_Pad1.18x1.45mm_HandSolder; MPN CL21B105KOFNNNE
C9: 4.7uF; C_0805_2012Metric_Pad1.18x1.45mm_HandSolder; MPN CL21A475KAQNNNE
C10, C11: 22pF; C_0805_2012Metric_Pad1.18x1.45mm_HandSolder; MPN CL21C220JBANNNC
D1: PWR vert; LED_0805_2012Metric_Pad1.15x1.40mm_HandSolder; MPN 150080GS75000
D2: RX vert; LED_0805_2012Metric_Pad1.15x1.40mm_HandSolder; MPN 150080GS75000
D3: TX jaune; LED_0805_2012Metric_Pad1.15x1.40mm_HandSolder; MPN 150080YS75000
F1: 500mA; Fuse_1206_3216Metric_Pad1.42x1.75mm_HandSolder; MPN MF-NSMF050-2
J1: USB_A; USB_A_CNCTech_1001-011-01101_Horizontal; MPN 1001-011-01101
J2: Bornier CAN; TerminalBlock_Phoenix_MKDS-1,5-3-5.08_1x03_P5.08mm_Horizont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; MPN 1729131 (MKDS 1,5/ 3-5,08)
J3: SWD; PinHeader_1x04_P2.54mm_Vertical; MPN 61300411121
JP1: TERM; PinHeader_1x02_P2.54mm_Vertical; MPN 61300211121
R1, R4, R5: 1k; R_0805_2012Metric_Pad1.20x1.40mm_HandSolder; MPN RC0805FR-071KL
R2: 0R; R_0805_2012Metric_Pad1.20x1.40mm_HandSolder; MPN RC0805JR-070RL
R3, R6: 10k; R_0805_2012Metric_Pad1.20x1.40mm_HandSolder; MPN RC0805FR-0710KL
R7: 120R; R_0805_2012Metric_Pad1.20x1.40mm_HandSolder; MPN RC0805FR-07120RL
SW1: RESET; SW_SPST_B3U-1000P; MPN B3U-1000P
SW2: BOOT0; SW_SPST_B3U-1000P; MPN B3U-1000P
U1: STM32G431KBT6; LQFP-32_7x7mm_P0.8mm; MPN STM32G431KBT6
U2: CH340C; SOIC-16_3.9x9.9mm_P1.27mm; MPN CH340C
U3: TJA1051T/3; SOIC-8_3.9x4.9mm_P1.27mm; MPN TJA1051T/3,118
U4: AMS1117-3.3; SOT-223-3_TabPin2; MPN AMS1117-3.3
U5: USBLC6-2SC6; SOT-23-6; MPN USBLC6-2SC6
Y1: 8MHz; Crystal_SMD_5032-2Pin_5.0x3.2mm; MPN quartz 8 MHz 5032, CL 16 pF (C10/C11 = 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

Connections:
+3V3: C2.1, C3.1, C5.1, C6.1, C7.1, C8.1, C9.1, C14.1, J3.4, R1.1, R2.1, SW2.1, U1.1 (VDD), U1.15 (VDDA), U1.17 (VDD), U2.16 (VCC), U3.5 (VIO), U4.2 (VO)
+5V: C1.1, C13.1, F1.2, U3.3 (VCC), U4.3 (VI), U5.5 (VBUS)
/BOOT0: R3.1, SW2.2, U1.31 (PB8)
/CANH: J2.3, R7.1, U3.7 (CANH)
/CANL: J2.2, JP1.2 (B), U3.6 (CANL)
/CH_V3: C4.1, R2.2, U2.4 (V3)
/OSC_IN: C10.1, U1.2 (PF0), Y1.1
/OSC_OUT: C11.1, U1.3 (PF1), Y1.2
/VBUS: F1.1, J1.1 (VBUS)
CAN_RX: U1.21 (PA11), U3.4 (RXD)
CAN_S: R6.1, U1.9 (PA4), U3.8 (S)
CAN_TX: U1.22 (PA12), U3.1 (TXD)
GND: C1.2, C2.2, C3.2, C4.2, C5.2, C6.2, C7.2, C8.2, C9.2, C10.2, C11.2, C12.2, C13.2, C14.2, D1.1 (K), D2.1 (K), D3.1 (K), J1.4 (GND), J1.5 (Shield), J2.1, J3.3, R3.2, R6.2, SW1.2, U1.14 (VSSA), U1.16 (VSS), U1.32 (VSS), U2.1 (GND), U3.2 (GND), U4.1 (GND), U5.2 (GND)
LED_RX: R4.1, U1.12 (PA7)
LED_TX: R5.1, U1.13 (PB0)
NRST: C12.1, SW1.1, U1.4 (PG10)
unnamed: D1.2 (A), R1.2
unnamed: D2.2 (A), R4.2
unnamed: D3.2 (A), R5.2
unnamed: JP1.1 (A), R7.2
SWCLK: J3.1, U1.24 (PA14)
SWDIO: J3.2, U1.23 (PA13)
UART_RX: U1.8 (PA3), U2.2 (TXD)
UART_TX: U1.7 (PA2), U2.3 (RXD)
USB_DM: J1.2 (D-), U2.6 (UD-), U5.3 (I/O2), U5.4 (I/O2)
USB_DP: J1.3 (D+), U2.5 (UD+), U5.1 (I/O1), U5.6 (I/O1)

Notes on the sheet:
G69 - ADAPTATEUR USB-CAN (remplace le CANable 2.0)
USB-A (clé) -> CH340C (UART 3,3 V) -> STM32G431KBT6 USART2 / FDCAN1 -> TJA1051T/3 -> bornier CAN_H / CAN_L / GND
Règles factory ENSEA : 2 couches, piste 0,4 mm, isolation 0,3 mm, vias 0,8/0,4 mm, cuivre nu. Carte 50 x 20 mm.
1 - USB, PROTECTION ET ALIMENTATION
2 - PONT USB-SÉRIE CH340C (mode 3,3 V : V3 relié à VCC par R2)
3 - STM32G431KBT6 (LQFP32, pas 0,8 mm)
DS12589 fig. 16 : VDD n x 100 nF + 4,7 uF (C5, C6, C9) ; VDDA 10 nF + 1 uF (C7, C8)
Quartz 8 MHz propre à l'adaptateur, distinct des 24 MHz des Nucleo :
référence d'horloge indépendante (bringup étape 6 bis). C10/C11 selon la CL du quartz.
BOOT0 maintenu + RESET : chargeur ST sur USART2 (PA2/PA3),
programmation par le CH340 sans sonde (à confirmer dans AN2606).
SWD : 1 SWCLK, 2 SWDIO, 3 GND, 4 3V3
4 - TRANSCEIVER ET CONNECTEUR CAN
R6 (près du MCU) : S à la masse = mode normal ; PA4 à 1 = mode silencieux.
JP1 fermé = terminaison 120 ohms (adaptateur en bout de bus).
J2 : bornier à vis 3 points, pas 5,08 mm. 1 GND, 2 CAN_L, 3 CAN_H.
Sur la carte, de haut en bas : H, L, G, comme le bornier de l'USBCAN-Z.
Carte 50 x 20 mm, composants sur les deux faces, sans trou de fixation.

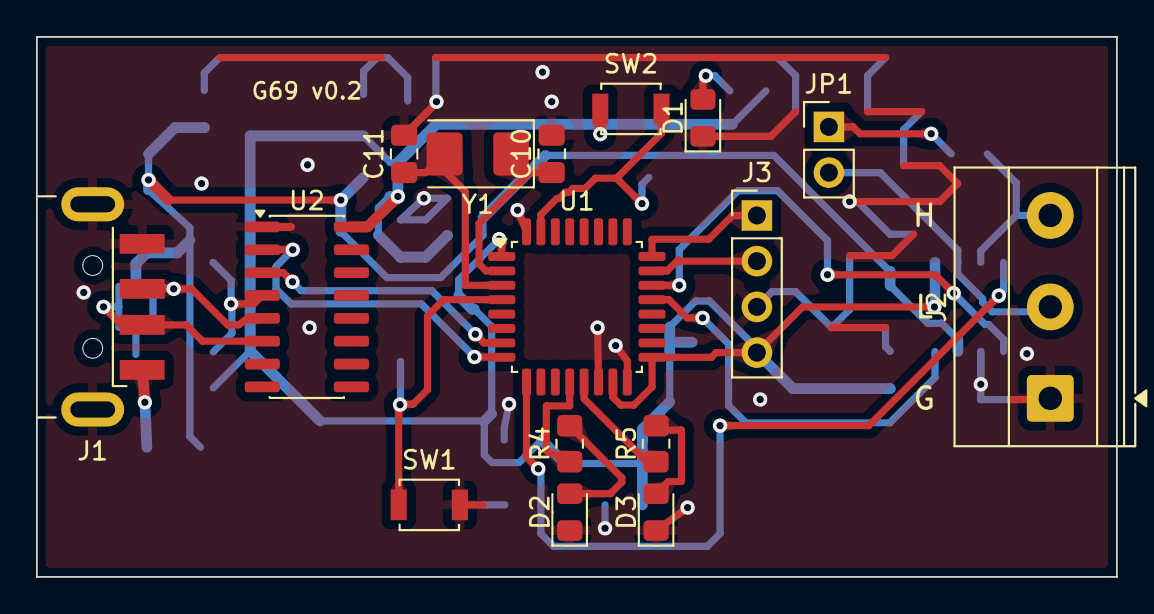
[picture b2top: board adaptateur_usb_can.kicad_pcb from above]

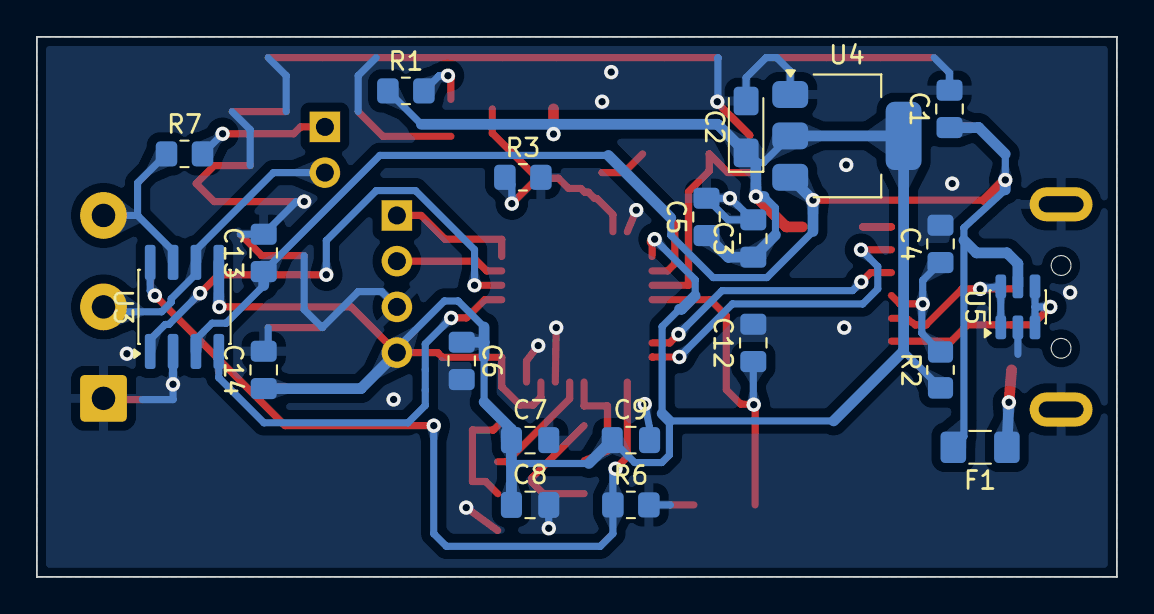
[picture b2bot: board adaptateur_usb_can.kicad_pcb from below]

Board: 2 copper layers, 60.0 x 30.0 mm, 37 parts (21 on the bottom side), 26 nets.

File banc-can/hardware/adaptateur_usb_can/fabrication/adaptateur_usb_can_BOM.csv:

Qté;Repères;Désignation;Valeur;Boîtier;Remarque
1;C1;Condensateur céramique X5R 16 V;10uF;0805;entrée 5 V du régulateur
2;C10, C11;Condensateur céramique C0G/NP0 50 V;22pF;0805;à ajuster selon la CL du quartz
1;C2;Condensateur tantale solide 22 µF 10 V, boîtier A (3216-18), polarisé;22uF;tantale A (3216);sortie de l'AMS1117 : tantale exigé pour la stabilité
7;C3, C4, C5, C6, C12, C13, C14;Condensateur céramique X7R 50 V;100nF;0805;découplage
1;C7;Condensateur céramique X7R 50 V;10nF;0805;VDDA, avec C8
1;C8;Condensateur céramique X7R 16 V;1uF;0805;VDDA
1;C9;Condensateur céramique X5R 10 V;4.7uF;0805;réservoir 3,3 V
1;D1;LED verte;PWR vert;0805;
1;D2;LED verte;RX vert;0805;
1;D3;LED jaune;TX jaune;0805;
1;F1;Fusible réarmable PTC, 500 mA maintenu, 6 V mini;500mA;1206;
1;J1;Fiche USB type A mâle coudée, pour CI (CNCTech 1001-011-01101);USB_A;traversant;branchement direct sur le PC
1;J2;Bornier à vis 3 points, pas 5,08 mm, pour CI (type Phoenix MKDS 1,5/3-5,08);Bornier CAN;traversant;bus CAN : H, L, G
1;J3;Barrette mâle sécable 1 × 4, pas 2,54 mm;SWD;traversant;SWCLK, SWDIO, GND, 3V3
1;JP1;Barrette mâle 1 × 2, pas 2,54 mm + cavalier;TERM;traversant;terminaison 120 Ω
3;R1, R4, R5;Résistance 1 %, 1/8 W;1k;0805;
1;R2;Résistance 0 Ω (ou strap);0R;0805;CH340C en mode 3,3 V
2;R3, R6;Résistance 1 %, 1/8 W;10k;0805;
1;R7;Résistance 1 %, 1/8 W;120R;0805;terminaison CAN
1;SW1;Bouton poussoir CMS 3 × 2,5 mm (Omron B3U-1000P);RESET;B3U;face avant
1;SW2;Bouton poussoir CMS 3 × 2,5 mm (Omron B3U-1000P);BOOT0;B3U;face avant
1;U1;Microcontrôleur STM32G431KBT6, LQFP32;STM32G431KBT6;LQFP-32;pas 0,8 mm
1;U2;Pont USB-UART CH340C, SOIC-16;CH340C;SOIC-16;version C : sans quartz externe
1;U3;Transceiver CAN TJA1051T/3, SOIC-8;TJA1051T/3;SOIC-8;suffixe /3 : broche VIO
1;U4;Régulateur linéaire 3,3 V AMS1117-3.3, SOT-223;AMS1117-3.3;SOT-223;
1;U5;Protection ESD USB USBLC6-2SC6, SOT-23-6;USBLC6-2SC6;SOT-23-6;
1;Y1;Quartz 8 MHz CMS 5 × 3,2 mm, 2 pastilles;8MHz;5032;noter sa capacité de charge CL

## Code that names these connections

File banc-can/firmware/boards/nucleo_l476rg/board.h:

/**
 * @file board.h
 * @brief Affectation des broches et de l'horloge — Nucleo-L476RG (MB1136), pont CAN-USB.
 *
 * Cette carte n'est pas un nœud du banc : elle sert d'**adaptateur** entre le bus
 * et le PC (`entry/slcan_bridge.c`, protocole slcan sur le port COM virtuel du
 * ST-LINK), à la place d'un CANable. Le STM32L476RG possède un bxCAN, le même
 * type de contrôleur que le F103 du nœud N4.
 *
 * Sources : UM1724 (Nucleo-64) et DS10198 (STM32L476xx). Ce qui n'a pas été
 * relu dans ces documents est marqué `TODO(verif)`.
 *
 * Connexions au bus :
 *
 *  | Signal  | Broche | Connecteur morpho    | Remarque                         |
 *  |---------|--------|----------------------|----------------------------------|
 *  | CAN1_RX | PA11   | CN10 broche 14       | AF9                              |
 *  | CAN1_TX | PA12   | CN10 broche 12       | AF9                              |
 *  | GND     | -      | CN10 broche 9 ou 20  | masse commune avec le bus        |
 *
 * `TODO(verif)` : numéros de broches de CN10 à confirmer dans UM1724 Table 19
 * avant câblage. PA11 et PA12 ne sont pas reliées au connecteur USB de la carte
 * (l'USB du L476 n'est pas utilisé), donc sans conflit.
 */

#ifndef BENCH_BOARD_H
#define BENCH_BOARD_H

#include "stm32l4xx_hal.h"

#define BENCH_BOARD_NAME "Nucleo-L476RG"

/* -------------------------------------------------------------------- horloge
 * HSE = 8 MHz fournis par le ST-LINK (broche MCO), configuration d'usine de la
 * carte (`TODO(verif)` : UM1724 §6.7, SB50/SB54/SB55). L'horloge est alors celle
 * d'un quartz ; si elle est absente, bench_clock_config() retombe sur le HSI16 et
 * le pont l'annonce (HSI non valide pour juger un débit).
 *
 * PLL : (8 MHz / 1) x 20 / 2 = 80 MHz. HSI : (16 MHz / 2) x 20 / 2 = 80 MHz.
 */
#define BENCH_HSE_HZ 8000000u
#define BENCH_HSI_HZ 16000000u

#define BENCH_SYSCLK_HZ 80000000u
#define BENCH_PCLK1_HZ  80000000u  /**< horloge du bxCAN */

/* ------------------------------------------------------------ temps de bit
 * 500 kbit/s : 80 MHz / 10 = 8 MHz, soit 16 quanta de 125 ns, point
 * d'échantillonnage à (1 + 13) / 16 = 87,5 % — le même que sur les autres
 * cartes. Les autres débits slcan (S0 à S8) gardent 16 quanta et changent le
 * prédiviseur : voir slcan_bridge.c.
 */
/** Prédiviseur de 500 kbit/s ; les autres débits slcan le recalculent (slcan_bridge.c). */
#define BENCH_CAN_PRESCALER 10u
#define BENCH_CAN_TSEG1 13u
#define BENCH_CAN_TSEG2 2u
#define BENCH_CAN_SJW   2u
#define BENCH_CAN_TQ_PER_BIT 16u

/* -------------------------------------------------------------------- CAN */
#define BENCH_CAN_RX_PORT GPIOA
#define BENCH_CAN_RX_PIN  GPIO_PIN_11
#define BENCH_CAN_TX_PORT GPIOA
#define BENCH_CAN_TX_PIN  GPIO_PIN_12
#define BENCH_CAN_AF      GPIO_AF9_CAN1

/** Pas de broche S de transceiver sur cette carte. */
#define BENCH_HAS_TRANSCEIVER_STANDBY 0

/* -------------------------------------------------------------------- LED */
/** LD2 (verte) = PA5 (UM1724 §6.5). Clignote à chaque trame transmise au PC. */
#define BENCH_LED_PORT GPIOA
#define BENCH_LED_PIN  GPIO_PIN_5
#define BENCH_LED_CLK_ENABLE() __HAL_RCC_GPIOA_CLK_ENABLE()
#define BENCH_LED_PULSE_MS 20u

/* ----------------------------------------------------- liaison avec le PC
 * Port COM virtuel du ST-LINK : USART2 sur PA2 (TX) et PA3 (RX), AF7 (UM1724
 * §6.8). C'est le canal slcan : rien d'autre ne doit y écrire (pas de printf).
 */
#define BENCH_HAS_SERIAL_LOG 0
#define BENCH_UART_INSTANCE  USART2
#define BENCH_UART_TX_PORT   GPIOA
#define BENCH_UART_TX_PIN    GPIO_PIN_2
#define BENCH_UART_RX_PORT   GPIOA
#define BENCH_UART_RX_PIN    GPIO_PIN_3
#define BENCH_UART_AF        GPIO_AF7_USART2
#define BENCH_UART_BAUD      115200u

/* Horloge fiable pour le CAN ? Renseigné à l'exécution par clock.c. */
#define BENCH_CLOCK_FIX_HINT \
    "Verifier que le ST-LINK fournit bien le MCO 8 MHz (UM1724, SB50/SB54/SB55)."

#endif /* BENCH_BOARD_H */
